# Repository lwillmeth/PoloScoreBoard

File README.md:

# PoloScoreBoard
A simple LED scoreboard for bike polo

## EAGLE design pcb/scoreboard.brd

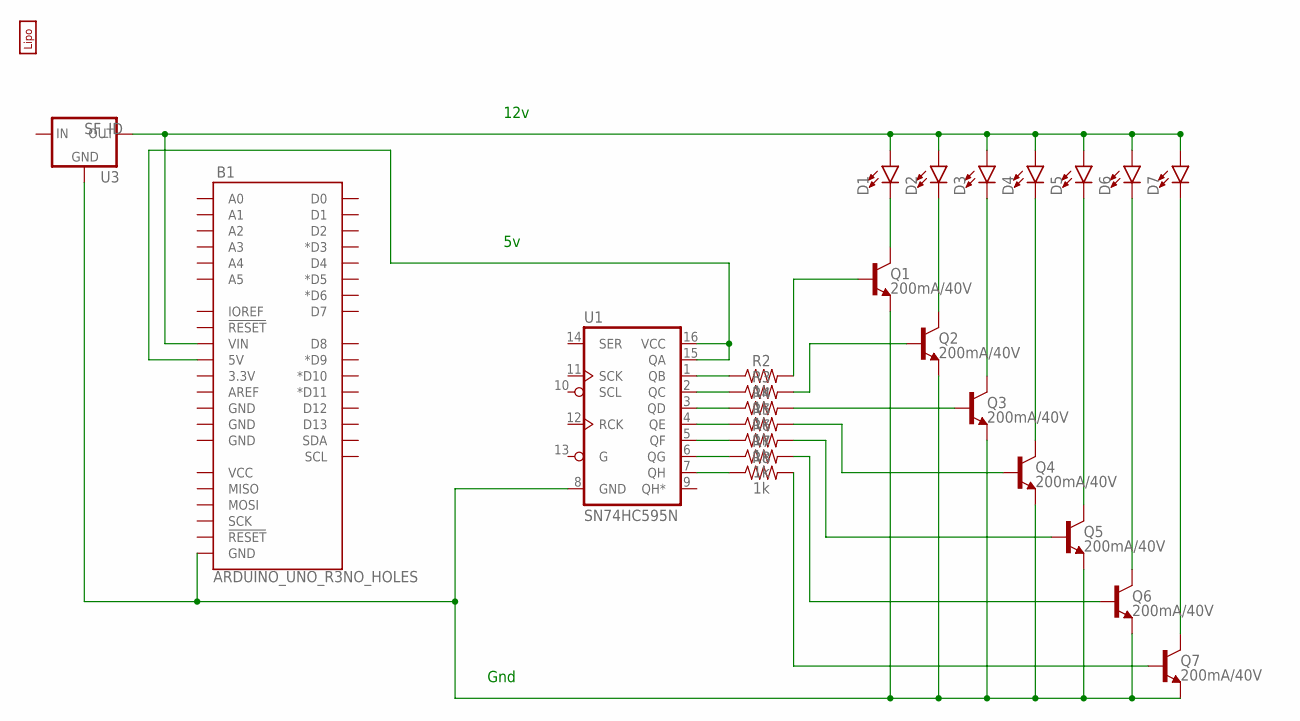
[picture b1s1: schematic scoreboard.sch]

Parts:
B1: ARDUINO_UNO_R3NO_HOLES; ARDUINO_R3_NO_HOLES
BT1: LIPO-OUTLINE2000; LIPO-2000
D1, D2, D3, D4, D5, D6, D7: LED3MM; LED_3MM
Q1, Q2, Q3, Q4, Q5, Q6, Q7: 200mA/40V; TO-92
R2, R3, R4, R5, R6, R7, R8: 1k; AXIAL-0.3
U1: SN74HC595N; DIP16
U3: V_REG_78XX-TO-220; TO-220-ALT

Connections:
unnamed: R2.P$1 (1), U1.1 (QB)
unnamed: R3.P$1 (1), U1.2 (QC)
unnamed: R4.P$1 (1), U1.3 (QD)
unnamed: R5.P$1 (1), U1.4 (QE)
unnamed: R6.P$1 (1), U1.5 (QF)
unnamed: R7.P$1 (1), U1.6 (QG)
unnamed: R8.P$1 (1), U1.7 (QH)
unnamed: B1.5V, U1.16 (VCC)
unnamed: B1.GND@1 (GND), Q1.1 (E), Q2.1 (E), Q3.1 (E), Q4.1 (E), Q5.1 (E), Q6.1 (E), Q7.1 (E), U1.8 (GND), U3.GND
unnamed: Q1.2 (B), R2.P$2 (2)
unnamed: Q2.2 (B), R3.P$2 (2)
unnamed: Q3.2 (B), R4.P$2 (2)
unnamed: Q4.2 (B), R5.P$2 (2)
unnamed: Q5.2 (B), R6.P$2 (2)
unnamed: Q6.2 (B), R7.P$2 (2)
unnamed: Q7.2 (B), R8.P$2 (2)
unnamed: D1.A, D2.A, D3.A, D4.A, D5.A, D6.A, D7.A, U3.OUT
unnamed: D1.K (C), Q1.3 (C)
unnamed: D3.K (C), Q3.3 (C)
unnamed: D4.K (C), Q4.3 (C)
unnamed: D5.K (C), Q5.3 (C)
unnamed: D6.K (C), Q6.3 (C)
unnamed: D7.K (C), Q7.3 (C)

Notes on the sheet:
12v
Gnd

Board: 2 copper layers, 25 parts (0 on the bottom side), 23 nets, no tracks yet.

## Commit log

2017-04-10 Add early Eagle pcb files
2017-04-10 Update schematics to add traces
2017-04-17 Simplify scoring code by moving more functionality into shiftOut()
2017-04-17 Begin adding button functionality
2017-04-18 Improve button code, test. It works!
2017-04-24 Adjust pins to match new pcb.
2017-04-24 Simplify duplicated statement, fix bug in 15 min timer.

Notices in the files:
parts and their libraries:
SparkFun-Boards: Licensing: Creative Commons ShareAlike 4.0 International - https://creativecommons.org/licenses/by-sa/4.0
